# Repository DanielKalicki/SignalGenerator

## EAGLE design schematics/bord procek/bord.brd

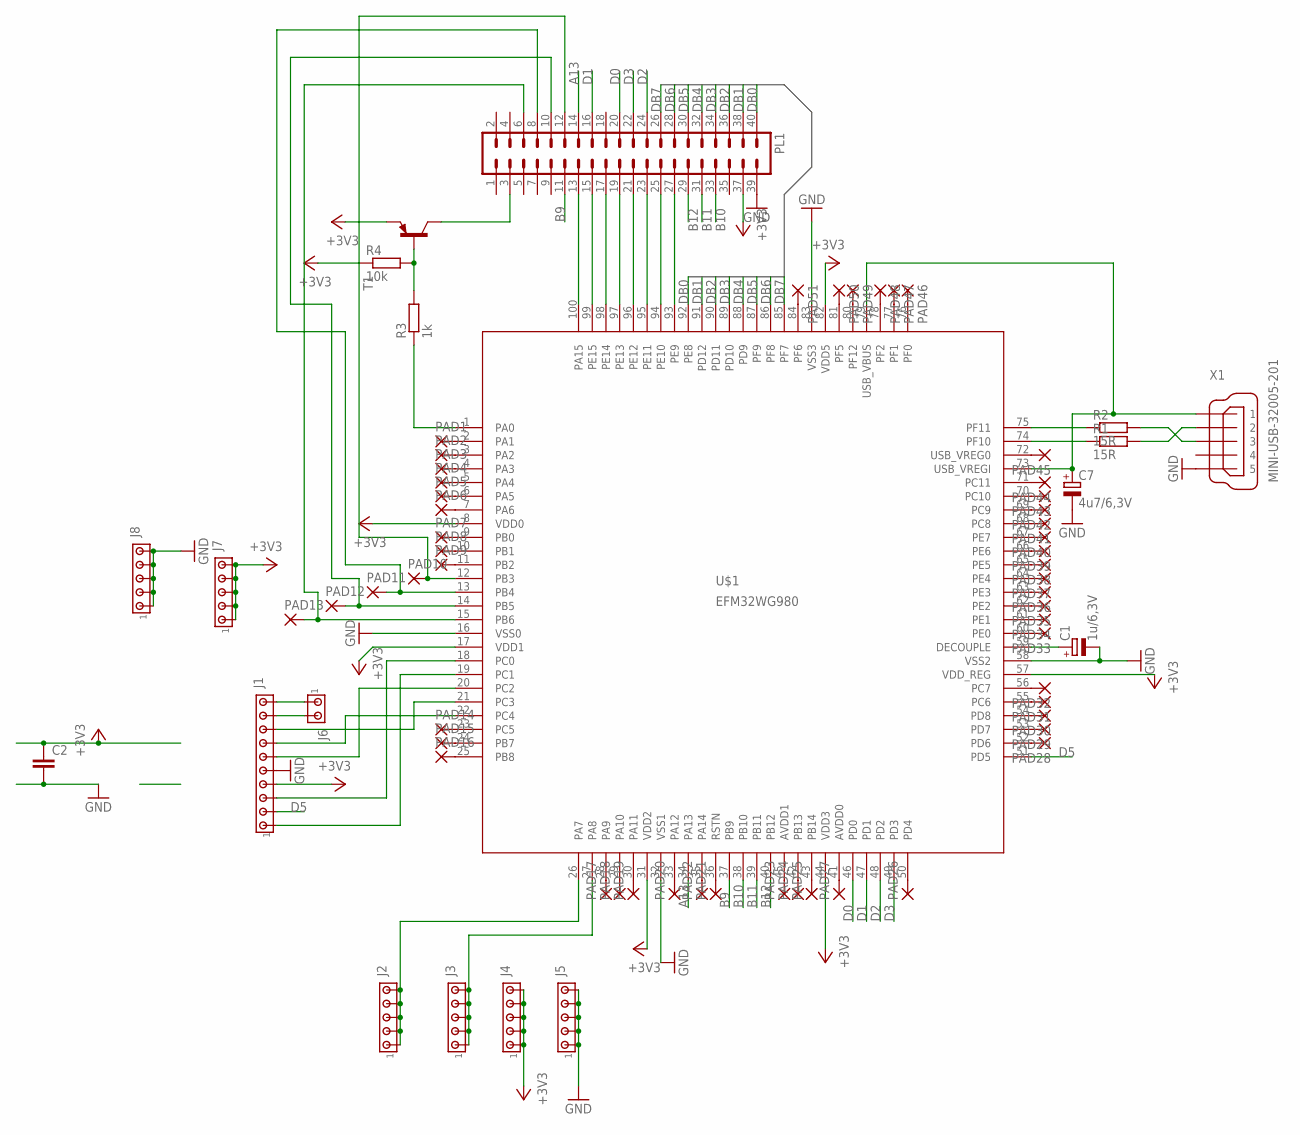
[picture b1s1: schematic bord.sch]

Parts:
C1: 1u/6,3V; SMC_B
C2: C-EUC0603; C0603
C7: 4u7/6,3V; SMC_B
J1: MTA10-100; 10X10MTA
J2, J3, J4, J5, J7, J8: MTA05-100; 10X05MTA
J6: MTA02-100; 10X02MTA
PAD1, PAD2, PAD3, PAD4, PAD5, PAD6, PAD7, PAD8, PAD9, PAD10, PAD11, PAD12, PAD13, PAD14, PAD15, PAD16, PAD17, PAD18, PAD19, PAD20, PAD21, PAD22, PAD23, PAD24, PAD25, PAD26, PAD27, PAD28, PAD29, PAD30, PAD31, PAD32, PAD33, PAD34, PAD35, PAD36, PAD37, PAD38, PAD39, PAD40, PAD41, PAD42, PAD43, PAD44, PAD45, PAD46, PAD47, PAD48, PAD49, PAD50, PAD51: 1,6/0,8
PL1: 40V
R1, R2: 15R; M0805
R3: 1k; M0805
R4: 10k; M0805
T1: BC807-16-PNP-SOT23-BEC; SOT23-BEC
U$1: EFM32WG980; LQFP100
X1: MINI-USB-32005-201; 32005-201

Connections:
+3V3: C2.1, J1.4, J4.1, J4.2, J4.3, J4.4, J4.5, J7.1, J7.2, J7.3, J7.4, J7.5, PL1.37, R4.1, T1.E, U$1.8 (VDD0), U$1.17 (VDD1), U$1.31 (VDD2), U$1.44 (VDD3), U$1.57 (VDD_REG), U$1.82 (VDD5)
A13: PL1.14, U$1.34 (PA13)
B9: PL1.11, U$1.37 (PB9)
B10: PL1.33, U$1.38 (PB10)
B11: PL1.31, U$1.39 (PB11)
B12: PL1.29, U$1.40 (PB12)
D0: PL1.20, U$1.46 (PD0)
D1: PL1.16, U$1.47 (PD1)
D2: PL1.24, U$1.48 (PD2)
D3: PL1.22, U$1.49 (PD3)
D5: J1.2, U$1.51 (PD5)
DB0: PL1.40, U$1.92 (PE8)
DB1: PL1.38, U$1.91 (PD12)
DB2: PL1.36, U$1.90 (PD11)
DB3: PL1.34, U$1.89 (PD10)
DB4: PL1.32, U$1.88 (PD9)
DB5: PL1.30, U$1.87 (PF9)
DB6: PL1.28, U$1.86 (PF8)
DB7: PL1.26, U$1.85 (PF7)
GND: C1.-, C2.2, C7.-, J1.5, J5.1, J5.2, J5.3, J5.4, J5.5, J8.1, J8.2, J8.3, J8.4, J8.5, PL1.39, U$1.16 (VSS0), U$1.32 (VSS1), U$1.58 (VSS2), U$1.83 (VSS3), X1.5
unnamed: C1.+, U$1.59 (DECOUPLE)
unnamed: J1.3, U$1.18 (PC0)
unnamed: J1.1, U$1.19 (PC1)
unnamed: PAD1.1, U$1.2 (PA1)
unnamed: PAD2.1, U$1.3 (PA2)
unnamed: PAD3.1, U$1.4 (PA3)
unnamed: PAD4.1, U$1.5 (PA4)
unnamed: PAD5.1, U$1.6 (PA5)
unnamed: PAD6.1, U$1.7 (PA6)
unnamed: R1.1, U$1.74 (PF10)
unnamed: R2.1, U$1.75 (PF11)
unnamed: R2.2, X1.3
unnamed: R1.2, X1.2
unnamed: C7.+, U$1.73 (USB_VREGI), U$1.79 (USB_VBUS), X1.1
unnamed: J1.7, U$1.22 (PC4)
unnamed: R3.2, R4.2, T1.B
unnamed: R3.1, U$1.1 (PA0)
unnamed: PL1.13, U$1.100 (PA15)
unnamed: PL1.15, U$1.99 (PE15)
unnamed: PL1.17, U$1.98 (PE14)
unnamed: PL1.19, U$1.97 (PE13)
unnamed: PL1.21, U$1.96 (PE12)
unnamed: PL1.23, U$1.95 (PE11)
unnamed: PL1.25, U$1.94 (PE10)
unnamed: PL1.27, U$1.93 (PE9)
unnamed: PL1.3, T1.C
unnamed: J1.6, U$1.20 (PC2)
unnamed: J1.8, U$1.21 (PC3)
unnamed: J2.1, J2.2, J2.3, J2.4, J2.5, U$1.26 (PA7)
unnamed: J3.1, J3.2, J3.3, J3.4, J3.5, U$1.27 (PA8)
unnamed: PAD7.1, U$1.9 (PB0)
unnamed: PAD8.1, U$1.10 (PB1)
unnamed: PAD9.1, U$1.11 (PB2)
unnamed: PAD10.1, PL1.12, U$1.12 (PB3)
unnamed: PAD11.1, PL1.8, U$1.13 (PB4)
unnamed: PAD12.1, PL1.10, U$1.14 (PB5)
unnamed: PAD13.1, PL1.6, U$1.15 (PB6)
unnamed: PAD14.1, U$1.23 (PC5)
unnamed: PAD15.1, U$1.24 (PB7)
unnamed: PAD16.1, U$1.25 (PB8)
unnamed: PAD17.1, U$1.28 (PA9)
unnamed: PAD18.1, U$1.29 (PA10)
unnamed: PAD19.1, U$1.30 (PA11)
unnamed: PAD20.1, U$1.33 (PA12)
unnamed: PAD21.1, U$1.36 (RSTN)
unnamed: PAD23.1, U$1.45 (AVDD1)
unnamed: PAD24.1, U$1.42 (PB13)
unnamed: PAD25.1, U$1.43 (PB14)
unnamed: PAD26.1, U$1.50 (PD4)
unnamed: PAD27.1, U$1.41 (AVDD0)
unnamed: PAD28.1, U$1.52 (PD6)
unnamed: PAD29.1, U$1.53 (PD7)
unnamed: PAD30.1, U$1.54 (PD8)
unnamed: PAD31.1, U$1.55 (PC6)
unnamed: PAD32.1, U$1.56 (PC7)
unnamed: PAD33.1, U$1.60 (PE0)
unnamed: PAD34.1, U$1.61 (PE1)
unnamed: PAD35.1, U$1.62 (PE2)
unnamed: PAD36.1, U$1.63 (PE3)
unnamed: PAD37.1, U$1.64 (PE4)
unnamed: PAD38.1, U$1.65 (PE5)
unnamed: PAD39.1, U$1.66 (PE6)
unnamed: PAD40.1, U$1.67 (PE7)
unnamed: PAD41.1, U$1.68 (PC8)
unnamed: PAD42.1, U$1.69 (PC9)
unnamed: PAD43.1, U$1.70 (PC10)
unnamed: PAD44.1, U$1.71 (PC11)
unnamed: PAD45.1, U$1.72 (USB_VREG0)
unnamed: PAD46.1, U$1.76 (PF0)
unnamed: PAD47.1, U$1.77 (PF1)
unnamed: PAD48.1, U$1.78 (PF2)
unnamed: PAD49.1, U$1.80 (PF12)
unnamed: PAD50.1, U$1.81 (PF5)
unnamed: PAD51.1, U$1.84 (PF6)
unnamed: PAD22.1, U$1.35 (PA14)
unnamed: J1.10, J6.1
unnamed: J1.9, J6.2

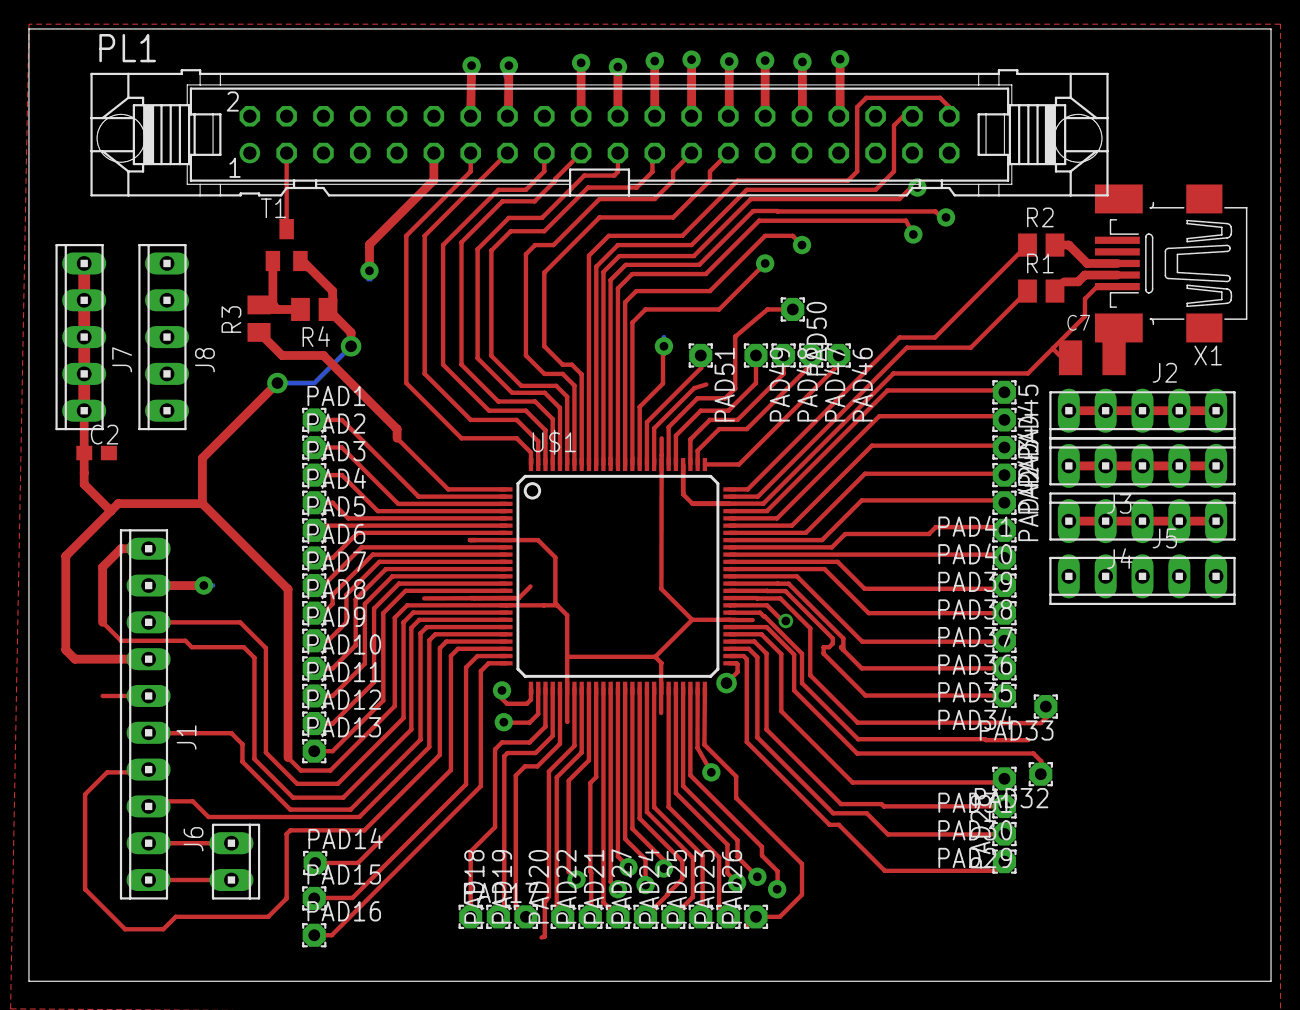
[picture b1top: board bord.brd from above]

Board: 2 copper layers, 85.7 x 65.7 mm, 70 parts (1 on the bottom side), 97 nets.

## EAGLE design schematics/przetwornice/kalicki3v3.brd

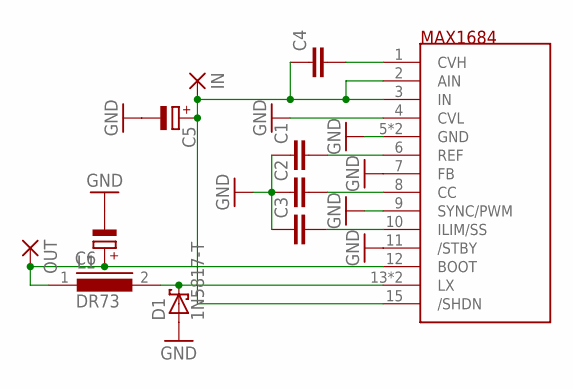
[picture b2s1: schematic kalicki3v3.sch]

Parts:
C1, C2, C3, C4: C-EUC0805; C0805
C5, C6: CPOL-EUE2.5-7; E2,5-7
D1: 1N5817-T; DO41-7.6
IN: 2,54/0,8
L1: DR73
OUT: 2,54/0,8
U$1: MAX1684; QSOP16

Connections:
GND: C1.1, C2.1, C3.1, C5.-, C6.-, D1.A, U$1.4 (CVL), U$1.5 (GND), U$1.7 (FB), U$1.9 (SYNC/PWM), U$1.11 (/STBY), U$1.16 (GND)
unnamed: C4.1, C5.+, IN.1, U$1.2 (AIN), U$1.3 (IN), U$1.15 (/SHDN)
unnamed: C3.2, U$1.10 (ILIM/SS)
unnamed: C2.2, U$1.8 (CC)
unnamed: C1.2, U$1.6 (REF)
unnamed: C4.2, U$1.1 (CVH)
unnamed: D1.C, L1.2, U$1.13 (LX), U$1.14 (LX)
unnamed: C6.+, L1.1, OUT.1, U$1.12 (BOOT)

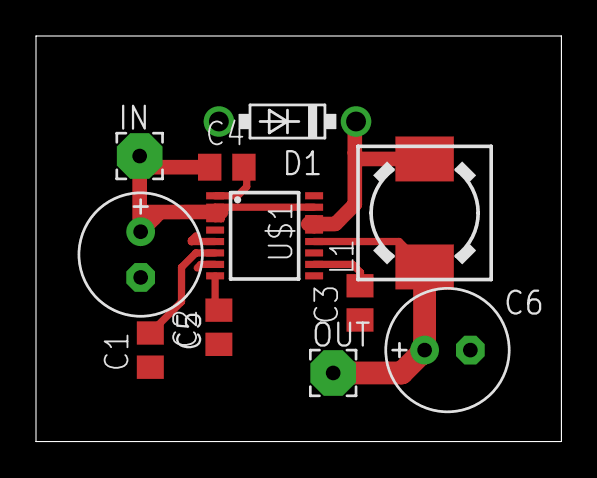
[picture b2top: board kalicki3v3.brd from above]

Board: 2 copper layers, 29.2 x 22.5 mm, 11 parts (0 on the bottom side), 8 nets.

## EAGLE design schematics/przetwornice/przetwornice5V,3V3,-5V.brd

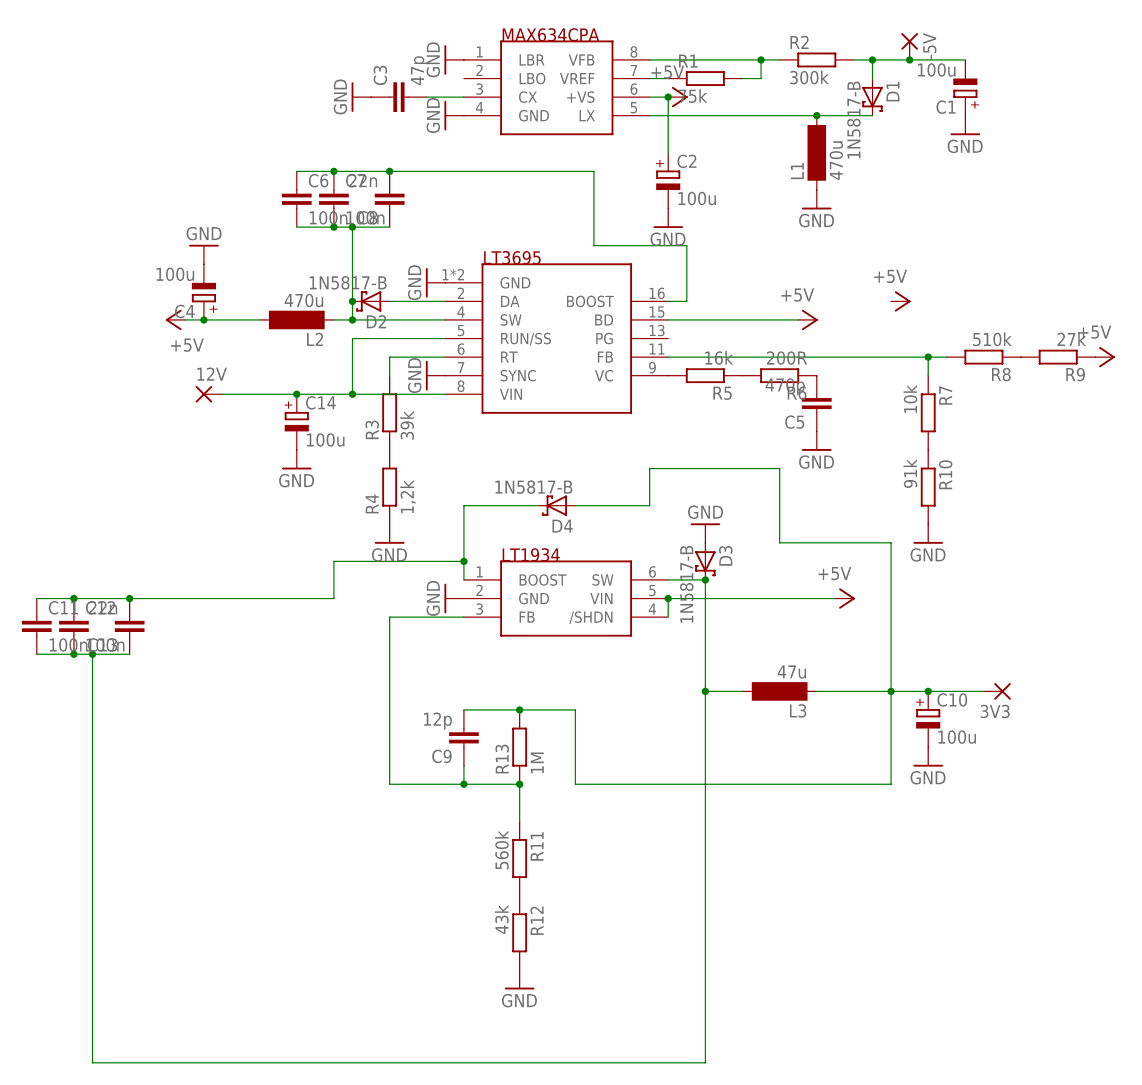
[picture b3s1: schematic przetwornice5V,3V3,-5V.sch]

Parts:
3V3, 12V: WIREPAD2,54/0,8; 2,54/0,8
-5V: WIREPAD2,54/0,8; 2,54/0,8
C1, C2, C4, C10, C14: 100u; E2,5-7
C3: 47p; C2.5-2
C5: 470p; C2.5-2
C6, C7, C11, C12: 100n; C0805
C8, C13: 22n; C2.5-2
C9: 12p; C2.5-2
D1, D2, D3, D4: 1N5817-B; DO41-7.6
L1, L2: 470u; MS50
L3: 47u; MS50
R1: 75k; R0805
R2: 300k; R0805
R3: 39k; R0805
R4: 1,2k; R0805
R5: 16k; R0805
R6: 200R; R0805
R7: 10k; R0805
R8: 510k; R0805
R9: 27k; R0805
R10: 91k; R0805
R11: 560k; R0805
R12: 43k; R0805
R13: 1M; 0207/10
U$1: MAX634CPA; DIL08
U$2: LT3695; MSOP16
U$3: LT1934; SOT23-6

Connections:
+5V: C2.+, C4.+, L2.2, R9.1, U$1.6 (+VS), U$2.15 (BD), U$3.4 (/SHDN), U$3.5 (VIN)
GND: C1.+, C2.-, C3.1, C4.-, C5.1, C10.-, C14.-, D3.A, L1.1, R4.1, R10.2, R12.2, U$1.1 (LBR), U$1.4 (GND), U$2.1 (GND), U$2.7 (SYNC), U$2.14 (GND), U$3.2 (GND)
unnamed: R1.1, U$1.7 (VREF)
unnamed: R1.2, R2.1, U$1.8 (VFB)
unnamed: -5V.1, C1.-, D1.A, R2.2
unnamed: D1.C, L1.2, U$1.5 (LX)
unnamed: C3.2, U$1.3 (CX)
unnamed: 12V.1, C14.+, U$2.5 (RUN/SS), U$2.8 (VIN)
unnamed: C11.2, C12.2, C13.1, D3.C, L3.2, U$3.6 (SW)
unnamed: D2.A, U$2.2 (DA)
unnamed: R3.1, R4.2
unnamed: R3.2, U$2.6 (RT)
unnamed: R5.2, U$2.9 (VC)
unnamed: R5.1, R6.2
unnamed: R7.1, R8.2, U$2.11 (FB)
unnamed: C5.2, R6.1
unnamed: R8.1, R9.2
unnamed: R7.2, R10.1
unnamed: C6.1, C7.1, C8.2, U$2.16 (BOOST)
unnamed: C6.2, C7.2, C8.1, D2.C, L2.1, U$2.4 (SW)
unnamed: R11.2, R12.1
unnamed: C9.1, R11.1, R13.1, U$3.3 (FB)
unnamed: C11.1, C12.1, C13.2, D4.C, U$3.1 (BOOST)
unnamed: 3V3.1, C9.2, C10.+, D4.A, L3.1, R13.2

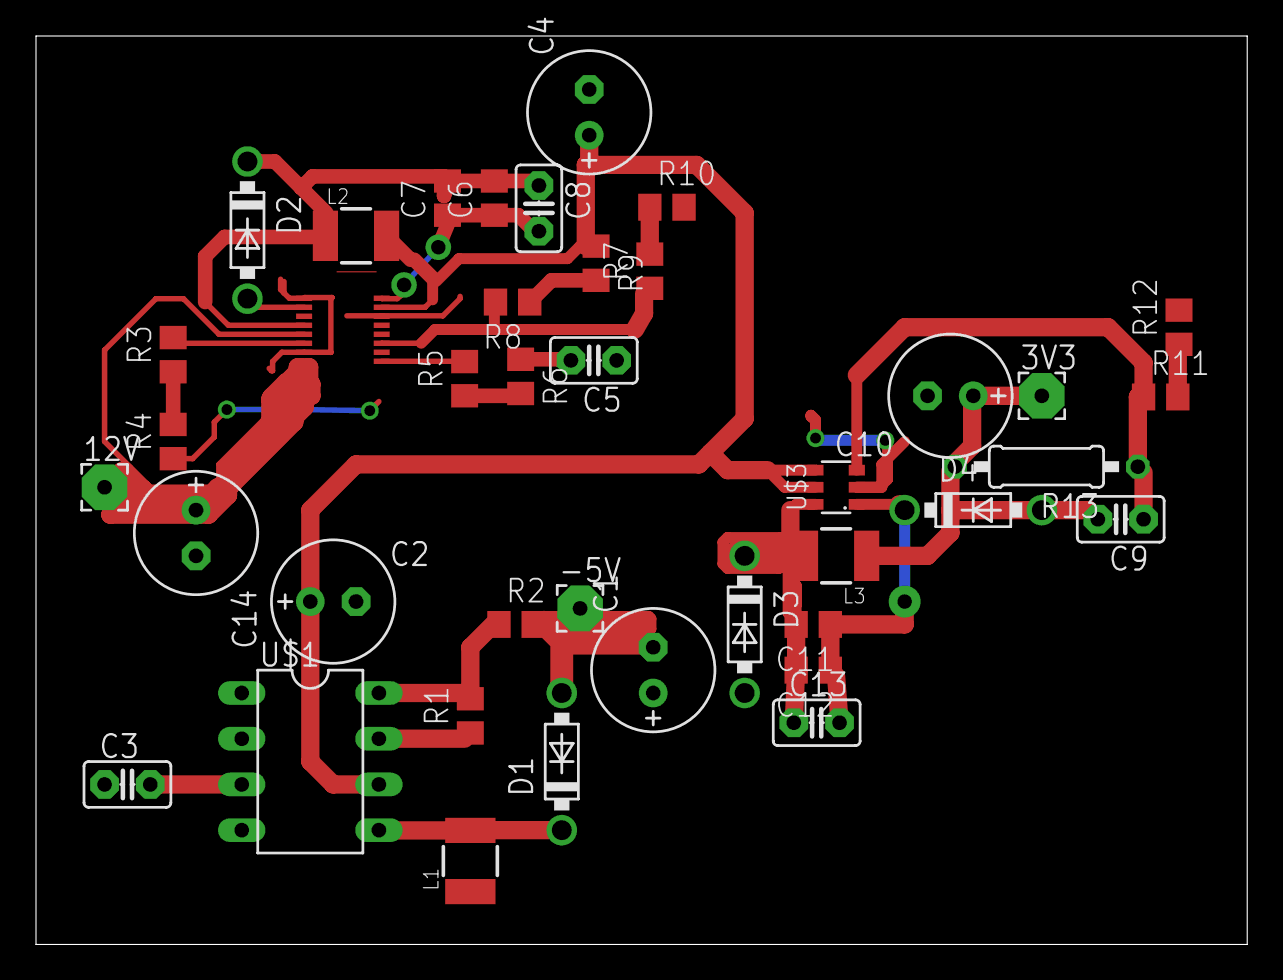
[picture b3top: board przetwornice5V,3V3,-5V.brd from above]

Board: 2 copper layers, 67.3 x 50.5 mm, 40 parts (0 on the bottom side), 24 nets.

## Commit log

2015-01-23 Added AD9106 waveform generator schematic and PCB layout
2015-01-25 first commit , first snippets of AD9106 library
2015-01-25 some registers descs added and updated , demo fired up
2015-01-26 spi simple driver added, catalog folder's name changed
2015-01-26 regsters description updated.
2015-01-27 Folder reorganization.
2015-02-01 first version of TFT library written (for driver SPFD5408)
2015-02-03 TFT didplay library - added support for both 8 and 16-bit bus
2015-02-04 first working version deployed
2015-02-05 TFT Display library works quite well. datasheet of LCD added
2015-02-06 projetc files content - removed linking of libraries
2015-02-07 DC voltage reference circuit (Opt001) added, Datasheets reorganization, schematic reorganization
2015-02-07 Datasheet reorganization
2015-02-07 reading 1 word via SPI added , added emLib libraries
2015-02-07 DC voltage reference board layout added.
2015-02-07 software implementation of SPI written. Seems the board doesn't respond correctly yet : ]
2015-02-13 Waveform generator - AD9106 registers read and write fixed. SDIO write implemented in software.
2015-02-14 DC voltage reference circuit update - 7508 pinout error fixed, 100nF caps added to op amps.
2015-02-14 Waveform generator - AD9106 output waveform working (tested with sawtooth and noise patterns).
2015-03-05 Optional modules description added.
2015-03-05 Opt004_500VSupply - basic step up converter schematic added based on LT3751.
2015-03-06 Opt007_CurrentOutput - Voltage to current converter based on Improved Howland Circuit added.
2015-03-07 Opt004_500VSupply - Schematic update - added DAC to control the output voltage. PCB layout added.
2015-03-07 Datasheets added for Opt004_500vSupply
2015-03-10 Opt004_500vSupply - resistors values update.
2015-03-11 library for ADS7843 - Touch Screen Controller, first version added
2015-03-11 ADS7843-TouchScreenController datasheet pushed
2015-03-12 Opt004_500VSupply - evaluation code for AVR microcontroller to test the on-board DAC.
2015-03-13 Touch controller works !
2015-03-13 Opt004_500VSupply - schematic resistor values fixed.
2015-03-15 Opt004_500VSupply - Voltage and Current sensing circuit added.
2015-03-16 Opt004_500VSupply - ADC for output current and voltage measurement changed to AD7682. PCB layout for output current and voltage measurement added.
2015-03-18 Opt004_500vSupply - datasheets added.
2015-03-18 Opt0012_PiezoDriver - piezoelectric driver module schematic and pcb layout based on a LT3572 ic added. LT3572 datasheet added.
2015-03-19 Opt004_500vSupply - Constant current mode added.
2015-03-19 Opt004_500vSupply - Constant current circuit PCB layout added.
2015-03-21 SignalGenerator optional modules - PCB layout and schematics converted to XPS files.
2015-03-22 Opt004_500vSupply - DAC changed to AD5664R, couples of series resistor added to feedback path to protect against voltage overloads.
2015-03-22 first port of FreeRtos kernel added
2015-03-23 FreeRtos Config file updated
2015-03-24 complete Freertos Kernel ported to our uC
2015-03-25 Opt004_500vSupply - Constant current mode simulation in MicroCap 9 added.
2015-03-26 clock changed to 32MHz , new Delay based on Timer0 added
2015-03-27 first battle with usb descriptors almost won ;) first version of CDC-Class implemented
2015-03-27 CDC usb descriptors finally set up correctly. CDC driver for windows added
2015-03-27 USB CDC finally done. Proper cdc driver prepared. usb debug useful method added.
2015-03-27 timer used for Delay(ms) changed from SysTick to Timer0
2015-03-28 LCD new much more robust setup added ! now works and looks quite well
2015-03-28 first snippets of implementation of Spi abstract layer done (hardware part)
2015-03-29 improvement in spi abstract layer solution - polling mode
2015-03-29 Front Panel - basic schematic added.
2015-03-29 software spi for touch panel controller added, ain't work correctly yet ---
2015-03-29 Front Panel - Schematic split into controller board and buttons/leds. PCB layout added.
2015-03-30 Front Panel - PCB layout update
2015-03-31 Front Panel - buttons & leds board finished.
2015-04-01 Front Panel - basic controller circuit and layout added.
2015-04-01 Touch panel - communication with the device works with some data mismatches.
2015-04-02 Front Panel - Controller board finished. Ground plane added to Front panel input board and controller board.
2015-04-02 Front panel - Schematics and PCB layout printed to XPS files.
2015-04-03 first hardware SPI version working with Touch controller
2015-04-03 Opt007_CurrentOutput - PCB layout added.
2015-04-04 touch panel minor improvement done - still SUCKS !!! Fuck that shit ! , AD9106 -> code making prettier - begun
2015-04-04 porting SPI abstract layer to ADS9106.
2015-04-05 Front panel - controller code added.
2015-04-08 schematy przetwornic
2015-04-09 Opt007_CurrentOutput - PCB update.
2015-04-10 First AD9106 working demo done ( SPI SOFTWARE version )
2015-04-11 First AD9106 working demo done ( SPI HARDWARE version )
2015-04-11 SPI communication for AD9106 finally done
2015-04-20 Boards pinout description added.
2015-04-22 Front Panel - uC initial code working.
2015-04-23 Pinout for our project added - finally ;)
2015-04-23 Pinout - microcontroller pins added.
2015-04-26 Front panel - errors in code fixed Pinout - LCD pinout added.
2015-04-27 first touch of SRAM- waveform storing
2015-04-27 MainMCU - sin output function added.
2015-04-27 SignalGeneratorMcuCode - Sin output working, basic SRAM update test code.
2015-04-29 SignalGeneratorMcuCode - SRAM pattern upload and pattern run working.
2015-05-04 Front panel - front panel acts as i2c slave.
2015-05-04 new graphic library added
2015-05-05 New graphic library, line drawning implemented
2015-05-07 draw Line finally implemented for new version of our graphical library
2015-05-10 first bitmap works with the new LCD library
2015-05-12 bord procek
2015-05-13 new LCD library finally works pretty well ; )
2015-05-15 Documentation added.
2015-05-16 first version of the library after PORTING hardware to the our homemade board
2015-05-17 freertos demo setup
2015-05-18 Demo with disabled touch controller prepared - PIN_BUSY added - did not help : (
